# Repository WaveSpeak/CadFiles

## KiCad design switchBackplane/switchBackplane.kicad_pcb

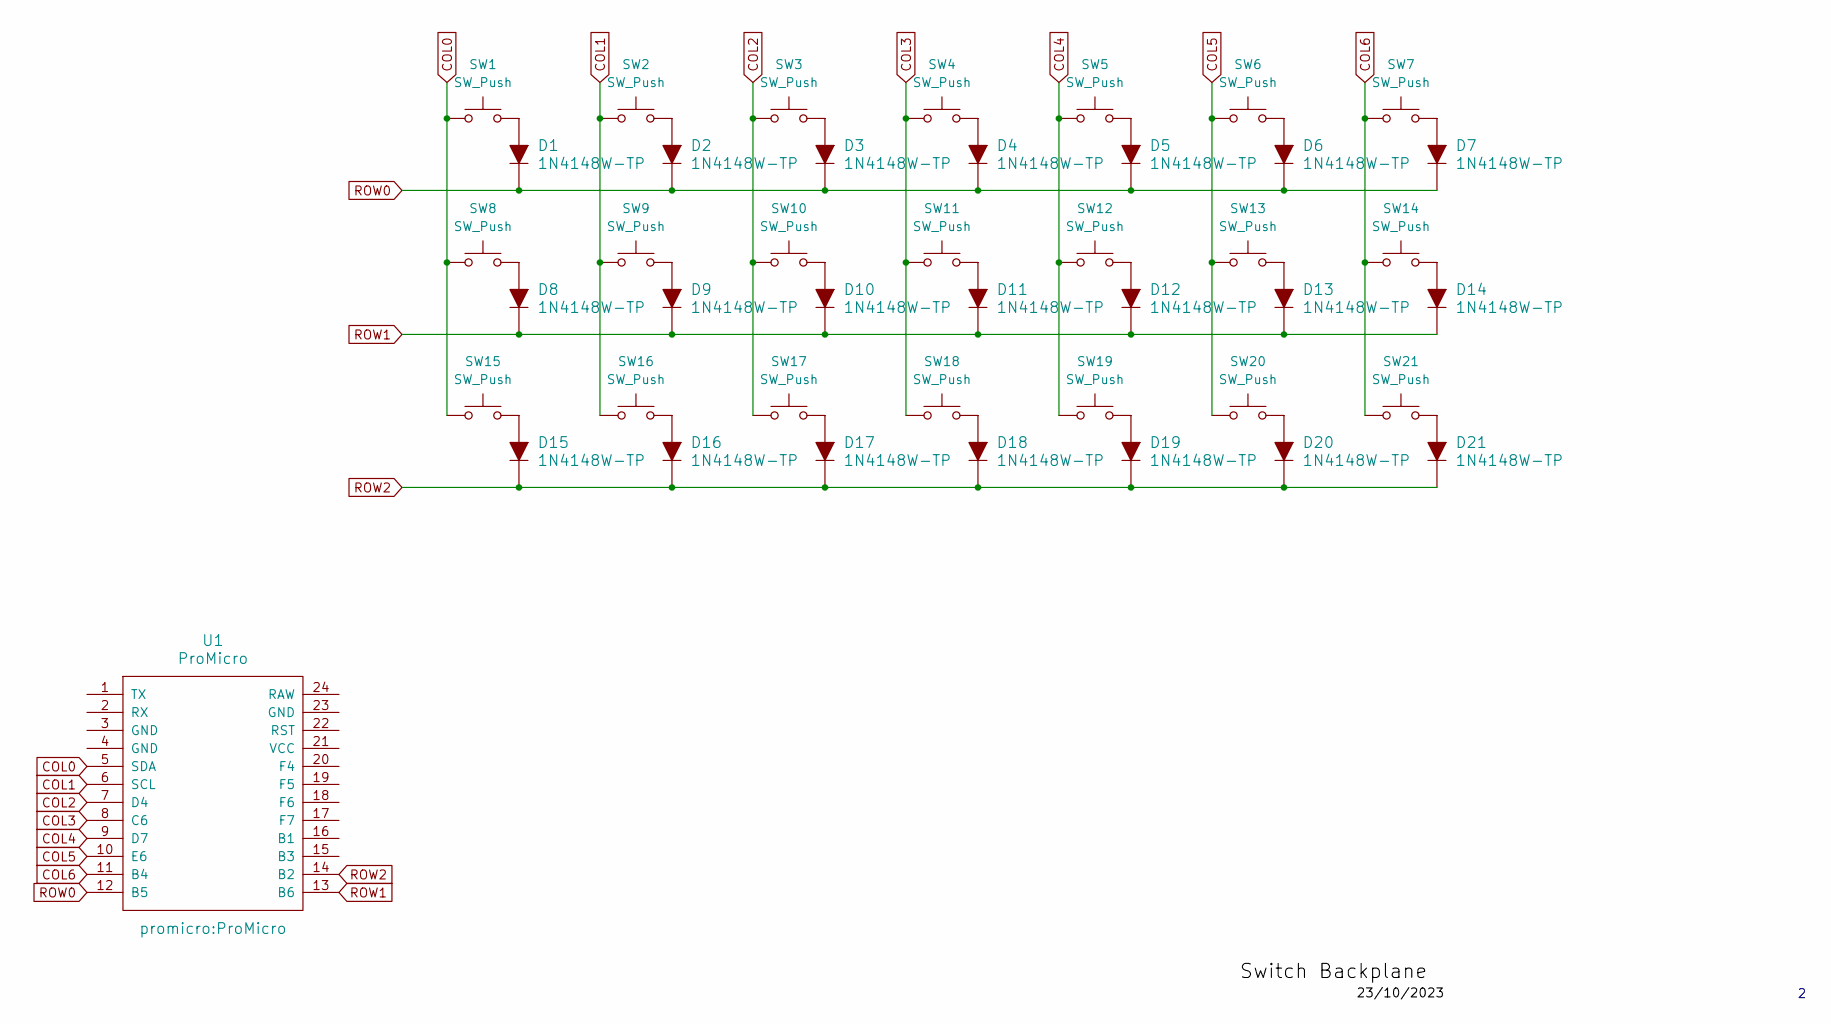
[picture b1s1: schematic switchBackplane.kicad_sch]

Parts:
D1, D2, D3, D4, D5, D6, D7, D8, D9, D10, D11, D12, D13, D14, D15, D16, D17, D18, D19, D20, D21: 1N4148W-TP; SOD-123; MPN 1N4148W-TP; Digi-Key_PN 1N4148WTPMSCT-ND
SW1, SW2, SW3, SW4, SW5, SW6, SW7, SW8, SW9, SW10, SW11, SW12, SW13, SW14, SW15, SW16, SW17, SW18, SW19, SW20, SW21: SW_Push; SW_223J
U1: ProMicro

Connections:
COL0: SW1.1, SW1.4, SW8.1, SW8.4, SW15.1, SW15.4, U1.5 (SDA)
COL1: SW2.1, SW2.4, SW9.1, SW9.4, SW16.1, SW16.4, U1.6 (SCL)
COL2: SW3.1, SW3.4, SW10.1, SW10.4, SW17.1, SW17.4, U1.7 (D4)
COL3: SW4.1, SW4.4, SW11.1, SW11.4, SW18.1, SW18.4, U1.8 (C6)
COL4: SW5.1, SW5.4, SW12.1, SW12.4, SW19.1, SW19.4, U1.9 (D7)
COL5: SW6.1, SW6.4, SW13.1, SW13.4, SW20.1, SW20.4, U1.10 (E6)
COL6: SW7.1, SW7.4, SW14.1, SW14.4, SW21.1, SW21.4, U1.11 (B4)
unnamed: D1.A, SW1.2, SW1.3
unnamed: D2.A, SW2.2
unnamed: D3.A, SW3.2
unnamed: D4.A, SW4.2
unnamed: D5.A, SW5.2
unnamed: D6.A, SW6.2
unnamed: D7.A, SW7.2
unnamed: D8.A, SW8.2, SW8.3
unnamed: D9.A, SW9.2
unnamed: D10.A, SW10.2
unnamed: D11.A, SW11.2
unnamed: D12.A, SW12.2
unnamed: D13.A, SW13.2
unnamed: D14.A, SW14.2
unnamed: D15.A, SW15.2, SW15.3
unnamed: D16.A, SW16.2
unnamed: D17.A, SW17.2
unnamed: D18.A, SW18.2
unnamed: D19.A, SW19.2
unnamed: D20.A, SW20.2
unnamed: D21.A, SW21.2
ROW0: D1.K, D2.K, D3.K, D4.K, D5.K, D6.K, D7.K, U1.12 (B5)
ROW1: D8.K, D9.K, D10.K, D11.K, D12.K, D13.K, D14.K, U1.13 (B6)
ROW2: D15.K, D16.K, D17.K, D18.K, D19.K, D20.K, D21.K, U1.14 (B2)

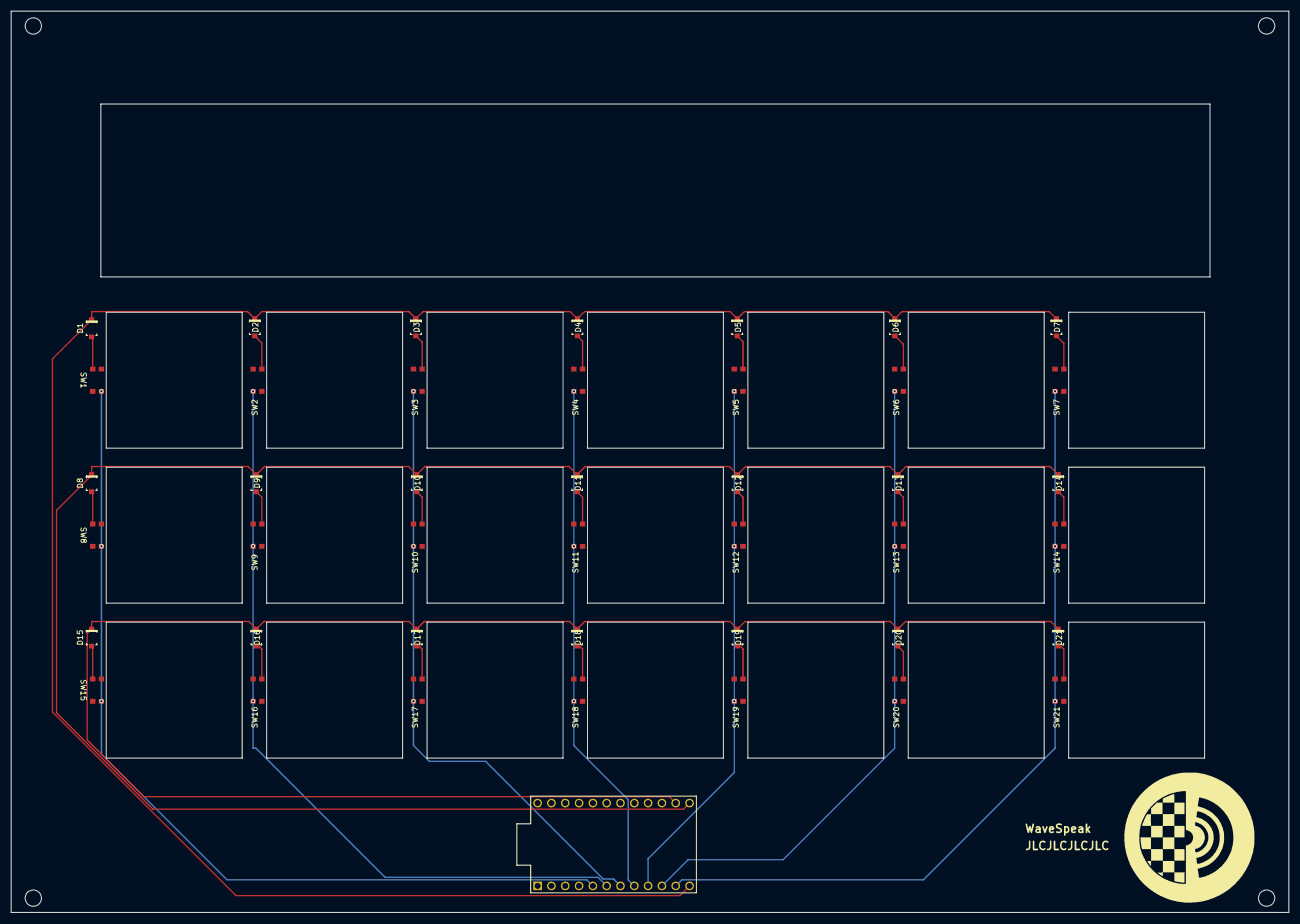
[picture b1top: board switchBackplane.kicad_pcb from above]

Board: 2 copper layers, 235.0 x 165.8 mm, 43 parts (0 on the bottom side), 31 nets.

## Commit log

2024-09-06 Add Main Cad File for case
2024-09-06 Create LICENSE
2024-09-06 Added KiCad files
2024-09-06 remove kicad files
2024-09-06 Add kicad files back
